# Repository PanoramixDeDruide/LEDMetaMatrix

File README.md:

# LEDMetaMatrix
KiCad &amp; Arduino source files for a matrix of LED matrices.

Be sure to remove any comments from your .PBM source files!

Code only works with ASCII PBM files.

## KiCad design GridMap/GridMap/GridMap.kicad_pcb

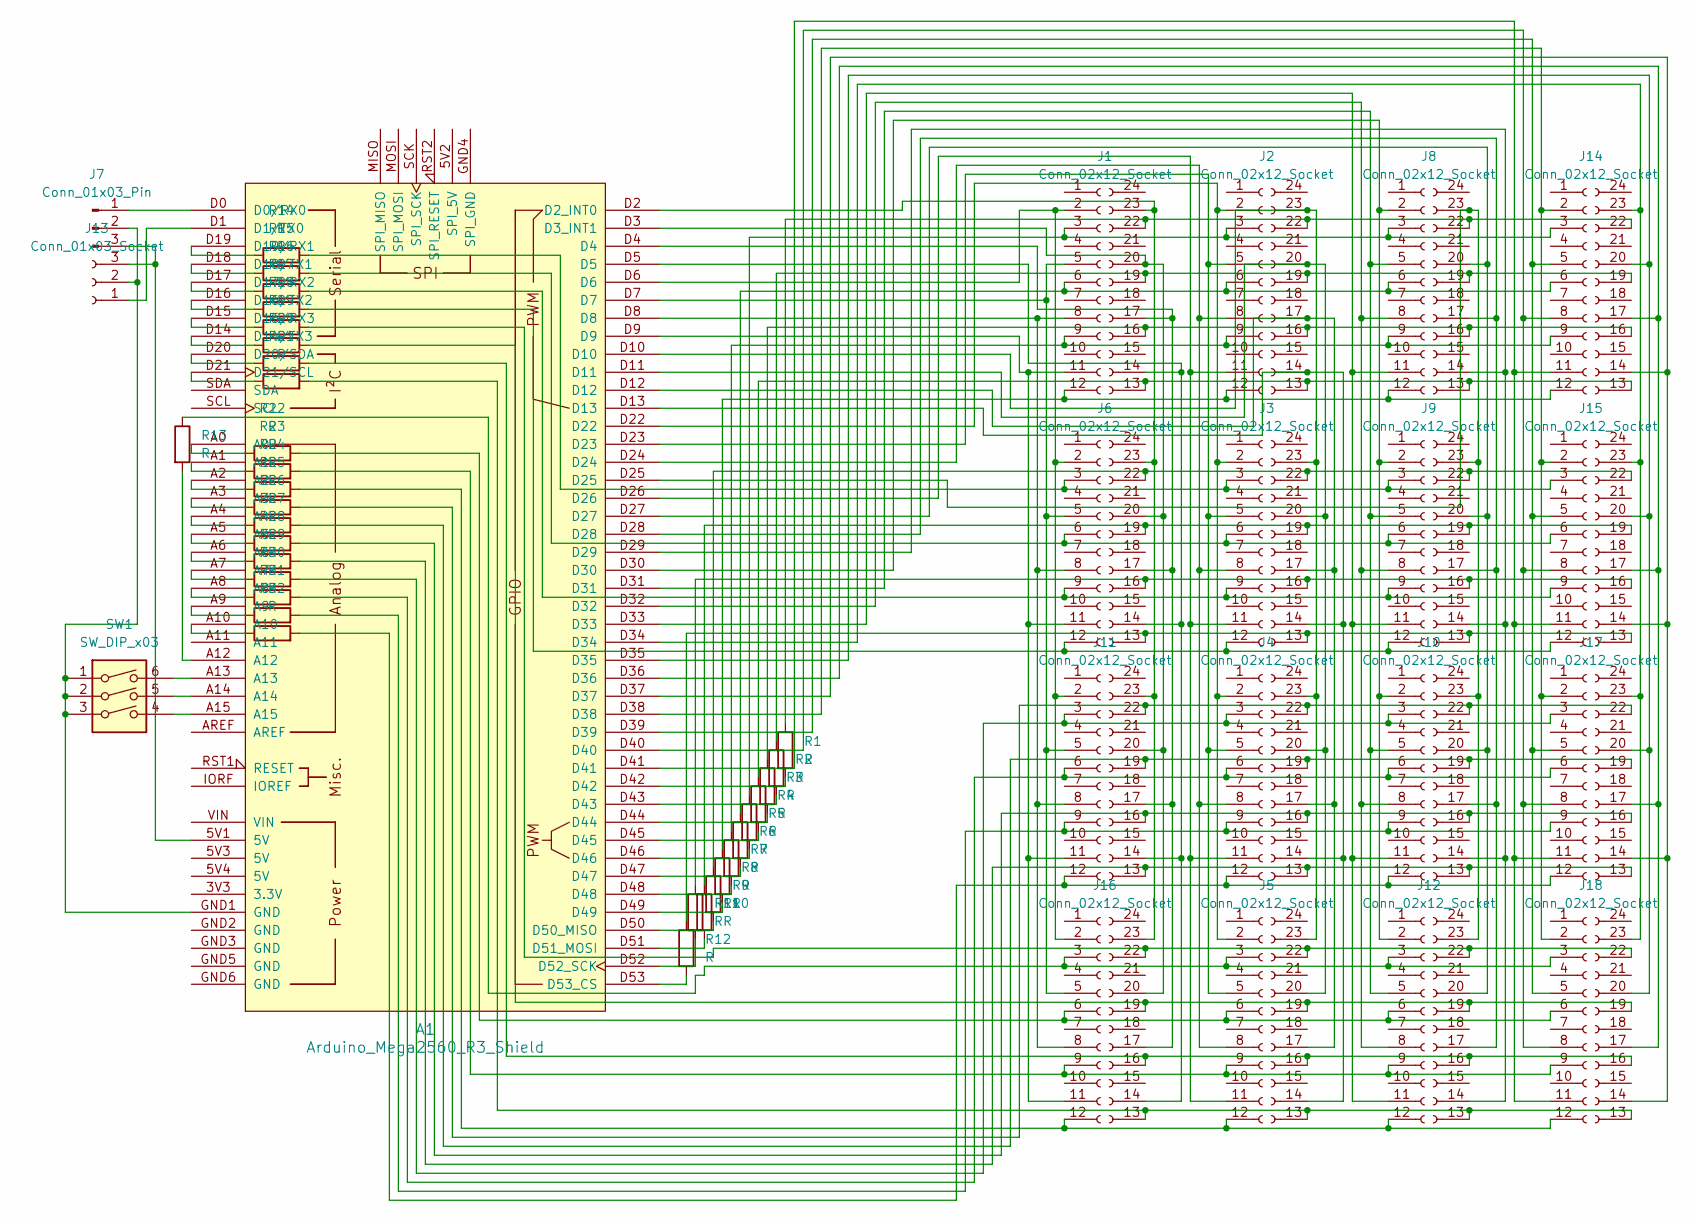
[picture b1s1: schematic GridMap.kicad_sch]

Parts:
A1: Arduino_Mega2560_R3_Shield
J1, J2, J3, J4, J5, J6, J8, J9, J10, J11, J12, J14, J15, J16, J17, J18: Conn_02x12_Socket; CSM-88181EG
J7: Conn_01x03_Pin; PinHeader_1x03_P2.54mm_Horizontal
J13: Conn_01x03_Socket; PinSocket_1x03_P2.54mm_Horizontal
R1, R2, R3, R4, R5, R6, R7, R8, R9, R10, R11, R12, R13, R14, R15, R16, R17, R18, R19, R20, R21, R22, R23, R24, R25, R26, R27, R28, R29, R30, R31, R32: R; R_Axial_DIN0207_L6.3mm_D2.5mm_P10.16mm_Horizontal
SW1: SW_DIP_x03; SW_DIP_SPSTx03_Slide_9.78x9.8mm_W7.62mm_P2.54mm

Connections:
unnamed: A1.D0 (D0/RX0), J7.1
unnamed: A1.D1 (D1/TX0), J13.1
unnamed: A1.D2 (D2_INT0), J1.23, J6.23, J11.23, J16.23
unnamed: A1.D3 (D3_INT1), J1.20, J6.20, J11.20, J16.20
unnamed: A1.D14 (D14/TX3), R19.1
unnamed: A1.D15 (D15/RX3), R18.1
unnamed: A1.D16 (D16/TX2), R17.1
unnamed: A1.D17 (D17/RX2), R16.1
unnamed: A1.D18 (D18/TX1), R15.1
unnamed: A1.D19 (D19/RX1), R14.1
unnamed: A1.D20 (D20/SDA), R20.1
unnamed: A1.D21 (D21/SCL), R21.1
unnamed: A1.D50 (D50_MISO), R9.2
unnamed: A1.D51 (D51_MOSI), R10.2
unnamed: A1.D52 (D52_SCK), R11.2
unnamed: A1.D53 (D53_CS), R12.2
unnamed: A1.A0, R22.1
unnamed: A1.A1, R23.1
unnamed: A1.A2, R24.1
unnamed: A1.A3, R25.1
unnamed: A1.A4, R26.1
unnamed: A1.A5, R27.1
unnamed: A1.A6, R28.1
unnamed: A1.A7, R29.1
unnamed: A1.A8, R30.1
unnamed: A1.A9, R31.1
unnamed: A1.A10, R32.1
unnamed: A1.A12, R13.2
unnamed: A1.A13, SW1.6
unnamed: A1.A14, SW1.5
unnamed: A1.A15, SW1.4
unnamed: A1.D42, R1.2
unnamed: A1.D43, R2.2
unnamed: A1.D44, R3.2
unnamed: A1.D45, R4.2
unnamed: A1.D46, R5.2
unnamed: A1.D47, R6.2
unnamed: A1.D48, R7.2
unnamed: A1.D49, R8.2
unnamed: A1.D6, J1.2, J6.2, J11.2, J16.2
unnamed: J1.3, J2.3, J8.3, J14.3, R5.1
unnamed: A1.D7, J1.5, J6.5, J11.5, J16.5
unnamed: J1.6, J2.6, J8.6, J14.6, R6.1
unnamed: A1.D8, J1.8, J6.8, J11.8, J16.8
unnamed: J1.9, J2.9, J8.9, J14.9, R7.1
unnamed: A1.D9, J1.11, J6.11, J11.11, J16.11
unnamed: J1.12, J2.12, J8.12, J14.12, R8.1
unnamed: J1.13, J2.13, J8.13, J14.13, R4.1
unnamed: A1.D5, J1.14, J6.14, J11.14, J16.14
unnamed: J1.16, J2.16, J8.16, J14.16, R3.1
unnamed: A1.D4, J1.17, J6.17, J11.17, J16.17
unnamed: J1.19, J2.19, J8.19, J14.19, R2.1
unnamed: J1.22, J2.22, J8.22, J14.22, R1.1
unnamed: A1.D22, J2.2, J3.2, J4.2, J5.2
unnamed: A1.D23, J2.5, J3.5, J4.5, J5.5
unnamed: A1.D24, J2.8, J3.8, J4.8, J5.8
unnamed: A1.D26, J2.11, J3.11, J4.11, J5.11
unnamed: A1.D13, J2.14, J3.14, J4.14, J5.14
unnamed: A1.D12, J2.17, J3.17, J4.17, J5.17
unnamed: A1.D11, J2.20, J3.20, J4.20, J5.20
unnamed: A1.D10, J2.23, J3.23, J4.23, J5.23
unnamed: A1.D30, J8.2, J9.2, J10.2, J12.2
unnamed: J4.3, J10.3, J11.3, J17.3, R29.2
unnamed: A1.D31, J8.5, J9.5, J10.5, J12.5
unnamed: J4.6, J10.6, J11.6, J17.6, R30.2
unnamed: A1.D32, J8.8, J9.8, J10.8, J12.8
unnamed: J4.9, J10.9, J11.9, J17.9, R31.2
unnamed: A1.D33, J8.11, J9.11, J10.11, J12.11
unnamed: J4.12, J10.12, J11.12, J17.12, R32.2
unnamed: J4.13, J10.13, J11.13, J17.13, R28.2
unnamed: A1.D29, J8.14, J9.14, J10.14, J12.14
unnamed: J4.16, J10.16, J11.16, J17.16, R27.2
unnamed: A1.D28, J8.17, J9.17, J10.17, J12.17
unnamed: J4.19, J10.19, J11.19, J17.19, R26.2
unnamed: A1.D27, J8.20, J9.20, J10.20, J12.20
unnamed: J4.22, J10.22, J11.22, J17.22, R25.2
unnamed: A1.D25, J8.23, J9.23, J10.23, J12.23
unnamed: J5.3, J12.3, J16.3, J18.3, R13.1
unnamed: J5.6, J12.6, J16.6, J18.6, R22.2
unnamed: J5.9, J12.9, J16.9, J18.9, R23.2
unnamed: J5.12, J12.12, J16.12, J18.12, R24.2
unnamed: J5.13, J12.13, J16.13, J18.13, R21.2
unnamed: J5.16, J12.16, J16.16, J18.16, R20.2
unnamed: J5.19, J12.19, J16.19, J18.19, R19.2
unnamed: J5.22, J12.22, J16.22, J18.22, R18.2
unnamed: A1.GND1 (GND), J7.2, J13.2, SW1.1, SW1.2, SW1.3
unnamed: A1.5V1 (5V), J7.3, J13.3
unnamed: A1.D38, J14.2, J15.2, J17.2, J18.2
unnamed: A1.D39, J14.5, J15.5, J17.5, J18.5
unnamed: A1.D40, J14.8, J15.8, J17.8, J18.8
unnamed: A1.D41, J14.11, J15.11, J17.11, J18.11
unnamed: A1.D37, J14.14, J15.14, J17.14, J18.14
unnamed: A1.D36, J14.17, J15.17, J17.17, J18.17
unnamed: A1.D35, J14.20, J15.20, J17.20, J18.20
unnamed: A1.D34, J14.23, J15.23, J17.23, J18.23
unnamed: J3.3, J6.3, J9.3, J15.3, R14.2
unnamed: J3.6, J6.6, J9.6, J15.6, R15.2
unnamed: J3.9, J6.9, J9.9, J15.9, R16.2
unnamed: J3.12, J6.12, J9.12, J15.12, R17.2
unnamed: J3.13, J6.13, J9.13, J15.13, R12.1
unnamed: J3.16, J6.16, J9.16, J15.16, R11.1
unnamed: J3.19, J6.19, J9.19, J15.19, R10.1
unnamed: J3.22, J6.22, J9.22, J15.22, R9.1

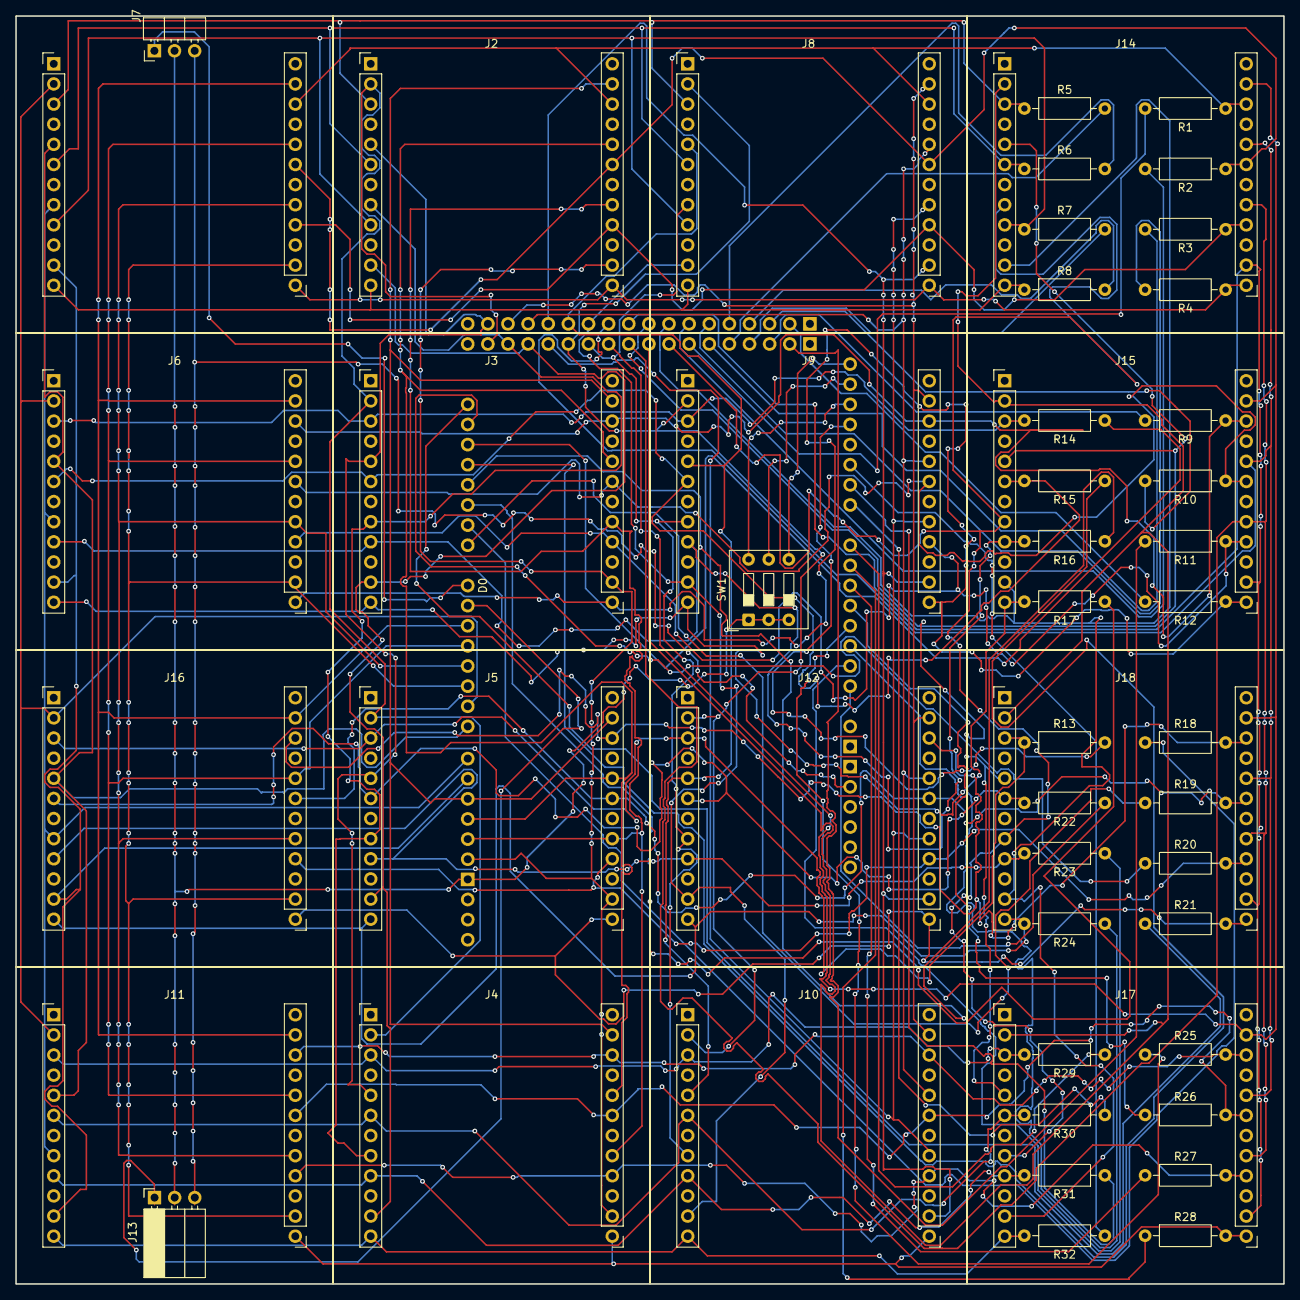
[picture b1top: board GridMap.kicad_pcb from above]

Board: 2 copper layers, 160.0 x 160.0 mm, 52 parts (0 on the bottom side), 103 nets.

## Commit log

2025-10-29 Added KiCad source files
2025-10-29 Added Arduino source file and KiCad footprint/symbol for CSM-88181EG LED matrix
2025-10-29 Added sample source files.
2025-10-29 Added proof of concept picture
2025-10-29 Added rough version of BOM, subject to change.
